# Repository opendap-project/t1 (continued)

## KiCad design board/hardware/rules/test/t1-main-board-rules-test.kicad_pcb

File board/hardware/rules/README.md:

# Main board rules

The T1 main board's own design rules, from the [PCB design constraints](../../docs/specs/pcb-design-constraints.md) (BRD-060). The sources of the manufacturing, assembly and reliability values are keyed at the end of this file.

- `t1-main-board.kicad_dru`: the product rules. Each rule is named after the constraint it enforces and the lowest quality level at which it is mandatory ([RFC 0010](https://github.com/opendap-project/rfcs/blob/main/text/0010-quality-levels.md)): `T1 PCB-H-01 [Q1]: …`.
- `netclasses.toml`: the net classes the rules and the schematic share, with their constraint IDs, design currents and impedance targets.
- `test/`: a test board with one failing and one passing object per rule, built by `make_test_board.py` on libs' `kicad/` test-board tools (submodule `../lib/opendap`).

The KiCad project's rules, [`../t1-main-board/t1-main-board.kicad_dru`](../t1-main-board/), are the composition of the PCBWay HDI fab rules (libs `kicad/` `design-rules/pcbway-hdi`), the OpenDAP craft rules (libs `kicad/` `design-rules/opendap-craft`) and these product rules, in that order, made and checked with `odapkit dru` from `t1-main-board.dru.toml`.

Impedance-controlled net classes are named `<name>_<ohms>D` (differential) or `<name>_<ohms>SE` (single-ended), so the craft rules exempt them from their general width rules (CRAFT-40, CRAFT-43; the composition was checked with every impedance class: no craft or fab report on their tracks). The product rules find the same classes with the same wildcards (PCB-S-14, PCB-W-01). `BAT_SENSE` also matches the `*_???SE` wildcard and is not an impedance class: the product rules leave it out by name.

## Layers

The board is the 6-layer [stackup v3](../../docs/specs/stackup-v3.md), with layer roles by zone (its §3). The rules name KiCad's layers:

| Stackup | L1 | L2 | L3 | L4 | L5 | L6 |
|---|---|---|---|---|---|---|
| KiCad | `F.Cu` | `In1.Cu` | `In2.Cu` | `In3.Cu` | `In4.Cu` | `B.Cu` |
| Role | signal (decoupling and core-rail pours in the core zone) | ground (core and system rails in the core zone) | ground (pours in the power zone) | signal (stripline; pours in the power zone, power or RF ground in the radio zone) | ground, full layer | signal |

Per-class widths are rules on `(layer outer)` (L1, L6) and `(layer inner)` (L4); PCB-S-14 keeps impedance classes off every other inner layer, so "inner" means L4 for them, and its zone rules keep them off L1 in the core zone and off L4 in the power and radio zones. Each width rule is min / opt / max = the stackup width −5 % / exact / +5 %: a 5 % width error moves the impedance by 2–3 %, a third of the fab's ±10 % window, so the rule catches a wrong width while leaving the fab's own corners alone. LPDDR4X keeps 3 × W from every other net on L4 (PCB-S-24). The ground layers of each zone take no other net's tracks or fills (PCB-S-25: L5 everywhere, L2 outside the core zone, L3 outside the power zone), and the I/O zone's `VBUS` nets stay on the outer layers (PCB-P-22).

## Severity

- A rule at Q0 or Q1 whose value has a source is an **error**.
- A rule at Q2 to Q4 is a **warning**, whatever its source (RFC 0010: items above the build's target level are debt, not blockers).
- A rule whose value is still **UNVERIFIED** is a **warning** at any level, and becomes an error when the value is sourced and the level is Q0 or Q1.

Each rule's comment in the `.kicad_dru` names its source; [Sources of the rule values](#sources-of-the-rule-values) lists the keys.

## Conventions the rules rely on

The rules find objects by reference prefix, footprint field, pad fabrication property and rule-area name. The schematic symbols and footprints carry them; a footprint that does not follow them escapes its rules.

| Object | Convention | Rules |
|---|---|---|
| Mounting hole | Footprint reference `H*` (`H1`…`H4`); one pad, NPTH or plated | PCB-H-01 to H-06 |
| Ceramic capacitor (MLCC) | Reference `C*`. A capacitor that is not an MLCC still gets the MLCC rules, which only cost distance | PCB-H-05, PCB-B-03 |
| Edge-mounted part | Reference `J*` (connectors) or `SW*` (side buttons): exempt from the part-to-edge rule, may overhang the edge | PCB-B-01 |
| BGA needing rework access | Footprint field `Rework` = `BGA` (RK3566, LPDDR4X, eMMC) | PCB-D-01 |
| BGA ball pads | Pad fabrication property "BGA pad" (also used by the fab rules) | PCB-H-06 |
| Fiducial | Reference `FID*`; pad fabrication property "Fiducial, global to board" or "Fiducial, local to footprint" | PCB-D-02 to D-04 |
| Test point | Reference `TP*`; pad fabrication property "Test point pad" | PCB-D-06 to D-09 |
| Via in a pad | Via property Filling = Filled and Capping = Capped (IPC-4761 type VII) | PCB-D-10 |
| Heat source | Footprint field `Thermal` = `hot` (converters, eFuses, charger, SoC, PMIC) | PCB-L-01 |
| Battery pocket | Rule area `BATTERY_POCKET`: the pocket's footprint on the board, grown by a 3 mm margin (**UNVERIFIED**) | PCB-L-01 |
| Battery contacts | Rule area `BATTERY_CONNECTOR`: the pocket-floor contact window plus 1 mm, around the six battery contacts and their unfused copper (ADR 0020) | PCB-L-02, L-05 |
| Battery nets | Net classes `PWR_BAT` (P+, P−) and `BAT_SENSE` (mid-cell tap, NTC) in `netclasses.toml` | PCB-L-02, L-05 |
| Empty contact position | Rule area `BATTERY_CONTACT_EMPTY`: the 7.00 × 2.70 mm pad position left empty between P+ and the mid-cell tap | PCB-L-04 |
| Battery contact ESD | Footprint field `ESD` = `battery` on the TPD1E10B06 of the mid-cell tap and NTC; rule area `BATTERY_ESD`: the contact pads grown by 3 mm (**UNVERIFIED**) | PCB-L-08 |
| Panel break tab | Rule area `BREAK_TAB` around each tab or mouse-bite position on the outline, reaching at least 5.08 mm (PCB-B-03) into the board | PCB-B-02, B-03 |
| RK3566 escape | Rule area `BGA_ESCAPE` (existing) | PCB-G-02, W-01, V-01 |
| Analog audio | Rule area `AUDIO_ANALOG` (existing) | PCB-A-07, A-20 |
| Differential pair | Net names ending in `_P` / `_N` (or `+` / `-`), so KiCad couples the pair | PCB-I-01, I-02, I-04, I-05 (pair gap) |
| RF ground cut-out | Rule area `RF_CUTOUT`: the L2 (L5) cut-out under the RF line, 1.6 mm wide and 0.6 mm past each end, on the cut layer and the pour layer of the line's side only (`In1.Cu` + `In2.Cu` for an L1 line, `In4.Cu` + `In3.Cu` for L6), with "keep out copper fills" set so the plane's fill stays out | PCB-R-03 |
| Zones | Rule areas `ZONE_CORE`, `ZONE_AUDIO`, `ZONE_POWER`, `ZONE_IO`, `ZONE_RADIO`, `ZONE_FACEPLATE` (one or more per zone, an area may cover only some layers) and `ZONE_CORRIDOR` ([floorplan v1](../../docs/specs/floorplan-v1.md)) | PCB-S-14 by zone, S-17, S-18, S-25, P-22 |
| Zone of a net | Net class `ZONE_<NAME>` or `ZONE_SHARED` besides the signal class (`netclasses.toml`) | PCB-S-17 |

## Check

```sh
PY=/Applications/KiCad/KiCad.app/Contents/Frameworks/Python.framework/Versions/Current/bin/python3
$PY hardware/rules/test/make_test_board.py
python3 hardware/lib/opendap/kicad/design-rules/tools/check_drc.py hardware/rules/test/t1-main-board-rules-test.kicad_pcb
```

Every rule fires exactly once in the FAIL column and nothing fires in the PASS column.

Rules that overlap the fab and craft rule sets are left to them: silkscreen to pads and vias, silk sizes, 45° routing, acute angles (CRAFT-41, 135° minimum), short segments and the via set live in libs `kicad/` `opendap-craft`. The composition `pcbway-hdi` + `opendap-craft` + these rules compiles under KiCad 10.0.7 with every T1 rule still firing on the test board. The test board has six copper layers (stackup v3); its GND objects are joined by a bus on L5 (`In4.Cu`, the full-layer ground, which takes GND), so the board reports no unconnected items.

## Not checked by DRC

Impedance itself, zone-local ground stitching and zone-boundary fences (PCB-S-19, S-13), the edge margin from a zone-local ground, the maximum pair gap, spacing to other nets (3–5 × W; LPDDR4X on L4 is DRC, PCB-S-24), length matching, skew and delay matching across layers (PCB-I, PCB-S-15), height zones (PCB-Z, including the battery-contact exception of PCB-L-05), copper area per net and via counts for current (PCB-P-01 to PCB-P-03, PCB-P-09), the battery contacts' pad size, pitch and order (PCB-L-04), via count per contact pad and pour symmetry (PCB-L-07), ESD distance (PCB-E-01) and test-pad coverage (PCB-T-02) are layout checks. The contact working height and the liner distance (PCB-L-06) are 3D review and case items. Review items are listed in the specification.

KiCad 10.0.7 can express three more rules, thermal-relief spoke count (`min_resolved_spokes`), differential-pair uncoupled length (`diff_pair_uncoupled`) and differential-pair gap (`diff_pair_gap`, with its maximum and the router's gap), but its report does not name the rule for them ("zone min spoke count", "(<rule> maximum uncoupled length", "(<rule> maximum gap"), so `check_drc.py` cannot attribute them. The pair gap's minimum is checked as a clearance instead (see Layers). They wait for a libs `kicad/` `check_drc.py` that reads those messages; until then they are CHK items below, with the other checks DRC cannot make.

## Review and script items (CHK)

Checklist wording; the level is the lowest at which the item is mandatory.

| ID | Level | Kind | Checklist wording |
|---|---|---|---|
| CHK-H-01 | Q1 | REV | The screw, washer and hole are chosen with the case; the PCB-H rules' 1.4 mm ring is recomputed from them, and H-01, H-02 become errors. |
| CHK-H-02 | Q2 | REV | Plated or non-plated mounting holes decided; if plated, on GND and stitched to the ground planes, and the case boss is insulating or its contact is part of the ESD path. |
| CHK-H-03 | Q1 | REV | No MLCC within the bending zone of a screw is oriented with its length towards the screw; parts near screws are placed with their long axis tangential to the hole. |
| CHK-B-01 | Q1 | REV | Tab and mouse-bite positions agreed with the fab's panel drawing; a `BREAK_TAB` area drawn at each, reaching 5.08 mm into the board. |
| CHK-B-02 | Q1 | REV | MLCCs within 5.08 mm of any broken edge lie parallel to the break line (KYOCERA AVX, Murata guidance; distance in PCB-B-03). |
| CHK-B-03 | Q1 | REV | Every part that overhangs the edge (J*, SW*) matches its case opening in the t1 interface files. |
| CHK-D-01 | Q1 | CHK | Three global fiducials per populated side, not symmetric, and two local fiducials at the RK3566 (PCB-M-09): count pads with the fiducial property per side. |
| CHK-D-02 | Q1 | REV | Polarity and pin-1 marks visible after assembly for every polarised part (diodes, tantalum or polymer capacitors, ICs, connectors). |
| CHK-D-03 | Q1 | REV | Paste on exposed thermal pads in a window pattern per each part's datasheet layout; coverage within the datasheet's range (**UNVERIFIED** generic figure, no IPC-7525 text retrieved). |
| CHK-D-04 | Q1 | CHK | Parts taller than the BGA within the rework clearance of a `Rework` = `BGA` part flagged from the 3D model heights. |
| CHK-D-05 | Q2 | CHK | Test pads 1.0 mm from component bodies (3D model outline), 5 mm from parts over 6.4 mm tall [JD]. |
| CHK-D-06 | Q1 | CHK | One test pad per net where required (PCB-T-02 rails, BRD-040 I2S, BRD-047 UART, BRD-015 SWD). |
| CHK-D-07 | Q1 | CHK | Via tenting set at board level (front and back tented), so only vias the layout opens on purpose are open; the fab order option matches. |
| CHK-D-08 | Q1 | CHK | Naming conventions followed: every mounting hole H*, fiducial pads carry the fiducial property, test pads the test-point property, BGA rework candidates and heat sources their fields. |
| CHK-W-01 | Q1 | CHK | Thermal relief on plane connections of connectors and test pads, at least 2 spokes resolved (PCB-G-07). KiCad `min_resolved_spokes` works but reports "zone min spoke count" without the rule name. |
| CHK-W-02 | Q2 | CHK | Differential-pair uncoupled length within the class limit. KiCad `diff_pair_uncoupled` works but reports "(<rule> maximum uncoupled length" without "rule '…'". The limit itself is **UNVERIFIED** (no source retrieved). |
| CHK-W-03 | Q2 | SIM | Via stubs over 0.30 mm on high-speed pairs simulated (Rockchip HSPCB p. 10 [RK]). |
| CHK-W-04 | Q2 | CHK | No test pad on a high-speed pair (Rockchip HSPCB p. 12 [RK]). Expressible in DRC as a later rule. |
| CHK-L-01 | Q0 | REV | `BATTERY_POCKET` drawn from the case's pocket outline plus the margin; the margin confirmed by the thermal analysis (V4-03). |
| CHK-V-01 | Q3 | REV | Creepage and clearance needs of IEC 62368-1 for the declared markets confirmed for ES1 circuits. |

## KiCad 10.0.7 behaviour found while testing

- **Angles are bare numbers.** `track_angle (min 90deg)` makes KiCad drop the whole file silently; `(min 90)` works. Each acute corner is reported twice, once per segment order.
- **A rule with `min 0` loses its name.** A `courtyard_clearance (min 0mm)` overlap is reported as the built-in "Courtyards overlap" without "(rule …)", so it cannot be tested; any value above zero is named.
- **Courtyards are measured from the line's centre; Edge.Cuts lines from their outer edge** in physical rules, and from their centre in `edge_clearance`.
- **Courtyard distance is per side.** A front part and a back footprint are not compared; hence the area-based PCB-L-01.
- **`physical_clearance` against a courtyard needs `A.Type == 'Footprint'`.** Without it the courtyard graphic and the footprint are both reported (two violations for one fault). A pad and a courtyard are on different layers and are never compared.
- **Silk to edge:** a silk line within the distance is reported only when the edge clips it; text is reported, but its distance to an internal cutout does not follow the text's position, so the test uses a clipped line.
- **`connection_width` fires** (tested with zone necks), but only about 0.01 mm or more below the limit; the test board uses 0.02 mm.
- **`min_resolved_spokes` and `diff_pair_uncoupled` work but are not named** in the report (CHK-W-01, CHK-W-02).
- **Unknown properties fail silently**: an assertion on a misspelt property fails on every object, which the PASS column catches. Via properties `Filling`, `Capping`, `Front_tenting`, `Back_tenting` and `Enable_Teardrops` exist with values `Filled`, `Capped`, `Tented`, `Not tented`.
- **`memberOfFootprint('H*')` is false for the footprint itself**; conditions on footprints use `Reference == 'H*'`.

## Sources of the rule values

Fetched 2026-10-24 unless stated.

| Key | Source | Kind |
|---|---|---|
| IPC | IPC-2221B Table 6-1 as reproduced in Altair Pollex documentation, "IPC Material": <https://help.altair.com/pollex/topics/pollex/verification/dfe_ipc_material_r.htm> | Secondary |
| F1 | ISO 7089 flat washer dimensions, fasten.it norm table: <https://www.fasten.it/en/norms/norm/iso_7089> (M2: d1 2.2, d2 5, h 0.3; M1.6: 1.7, 4, 0.3) | Secondary (vendor copy of the standard) |
| MU | Murata FAQ on chip capacitor mounting near screw holes: <https://www.murata.com/en-global/support/faqs/capacitor/ceramiccapacitor/mnt/0030> and the GRM data-sheet caution ("as far away from the screw holes as possible") | Primary |
| DK | DigiKey TechForum, "Ceramic Capacitor Failure: Design Solutions & Mitigating Board Flex Cracking", quoting KYOCERA AVX: <https://forum.digikey.com/t/ceramic-capacitor-failure-design-solutions-mitigating-board-flex-cracking/26195> | Secondary |
| JL | JLCPCB PCB capabilities (Legend, Outline, panelisation): <https://jlcpcb.com/capabilities/pcb-capabilities> | Primary (another fab) |
| JD | JLCPCB blog, "PCB Test Points and Smart DFT": <https://jlcpcb.com/blog/pcb-test-points-and-smart-dft> | Secondary |
| LC | LCSC blog, "How to Properly Place Fiducial Marks on PCBs": <https://www.lcsc.com/blog/how-to-properly-place-fiducial-marks-on-pcbs-a-step-by-step-guide/> | Secondary |
| AP | ALLPCB, "Non-Plated Through Holes: Design Rules": <https://www.allpcb.com/allelectrohub/non-plated-through-holes-design-rules-for-optimal-performance-and-reliability> | Secondary |
| RK | Rockchip RK3568 High Speed PCB Design Guide V1.0.0, cited by page | Primary |
| P1–P20 | The prototype fab's published pages, as keyed in libs' `kicad/` `pcbway-*` rule sets (fetched 2026-10-22): P1 capabilities, P2 advanced, P3 HDI, P11 via-in-pad, P16 order options, P20 assembly reminders | Primary |
| KiCad | KiCad 10.0.7 PCB Editor manual, custom rules (bundled `pcbnew.html`), and the behaviour listed above | Primary |

Not retrieved, so not used for any value: IPC-7351B courtyard excess table, IPC-7095 rework clearances, IPC-A-610, IPC-2152, IPC-7525 paste, SMEMA 3.1 text, TI and Intel high-speed layout guides for uncoupled length, the fab's pages on fiducials, test points and tab clearance, and any Li-ion cell maker's heat-source distance.

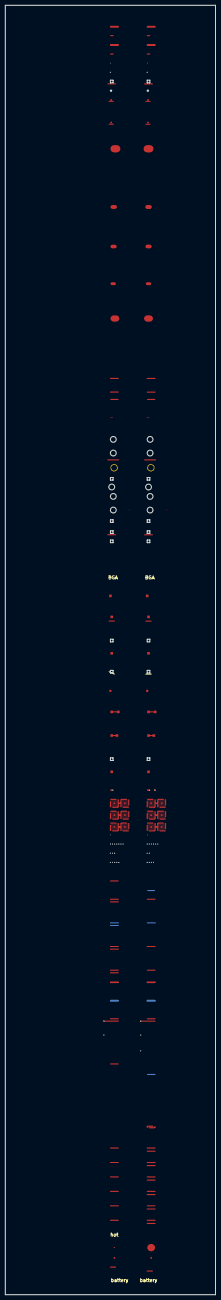
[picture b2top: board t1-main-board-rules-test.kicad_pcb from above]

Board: 6 copper layers, 80.0 x 490.7 mm, 74 parts (0 on the bottom side), 10 nets.

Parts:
C1, C2, C3, C4, C5, C6: test
D1, D2: test
FID1, FID2: test
H1, H2, H3, H4, H5, H6, H7, H8, H9, H10, H11, H12, H13, H14: test
R1, R2, R3, R4, R5, R6, R7, R8, R9, R10, R11, R12, R13, R14, R15, R16, R17, R18, R19, R20, R21, R22, R23, R24, R25, R26, R27: test
TP1, TP2, TP3, TP4, TP5, TP6, TP7, TP8, TP9, TP10, TP11, TP12, TP13, TP14: test
U1, U2, U3, U4, U5, U6, U7, U8, U9: test

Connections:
DDR_50SE_1: R18.1, R19.1
DDR_50SE_2: R20.1, R21.1
N49: TP7.1, TP8.1
N50: TP9.1, TP10.1
N51: R9.1, TP11.1
N52: R10.1, TP12.1
N58: R14.1, R15.1
N59: R16.1, R17.1
N60: R22.1, R23.1
N61: R24.1, R25.1

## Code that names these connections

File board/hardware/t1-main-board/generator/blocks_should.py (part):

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    grp(col, lambda: link_group(s, "LINK_M", "vcc3v3_sys", "HAPTIC_VDD", variants, "Link #19"))
    grp(col, pads(s, "LRA contacts (BOM v1 line 124)", ("LRA_P", "LRA_N")))
    s.iface_rows = [["I2C2_SCL, I2C2_SDA", "Bidirectional", "0x5A; pull-ups on blk.soc-pmuio"],
                    ["HAPTIC_EN", "Input", "Expander P04, pulled down on blk.gpio-expander: standby"]]
    s.rail_rows = [["HAPTIC_VDD", "1 µF", "SLOS854D Table 32"], ["HAPTIC_REG", "1 µF", "SLOS854D Table 32"]]
    corner_notes(s, [
        "1. Function: DRV2605L closed-loop LRA driver with auto-resonance (BRD-058, should) for the",
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
def draw_tpm(s, variants):
    f = Flow(s)
    pins = {"SCL": "I2C2_SCL", "SDA": "I2C2_SDA", "RST#": "TPM_RST_N", "TEST#": "TPM_VDD",
            "GPIO_00": None, "GPIO_01": None, "GPIO_02": None, "NCI": None, "NC": None, "I2C_PIRQ#": "TPM_PIRQ_N",
            "VDD": "TPM_VDD", "NCI/VDD": "TPM_VDD", "GND": "GND", "NCI/GND": "GND", "EP": "GND"}
    grp(f, lambda: ic_group(
        s, "SLB9673 TPM 2.0 at I2C2 0x2E (BOM v1 line 122)", "infineon", "SLB9673XU20FW2613XTMA1", pins,
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              [("R_2k2", "TPM_VDD", "TPM_RST_N")]], pad_left=15.24, rows_dx=5.08))
    grp(f, lambda: link_group(s, "LINK_M", "vcca1v8_pmu", "TPM_VDD", variants, "Link #20"))
    s.iface_rows = [["I2C2_SCL, I2C2_SDA", "Bidirectional", "0x2E; pull-ups on blk.soc-pmuio"],
                    ["TPM_RST_N", "Input", "GPIO0_D3; 2.2 kΩ pull-up here wins over the SoC pull-down"],
                    ["TPM_PIRQ_N", "Output", "Open drain; pull-up on vcc_1v8 on blk.soc-vccio-a"]]
    s.rail_rows = [["TPM_VDD", "1 µF + 3 x 100 nF", "SLB9673 DS Figure 2"]]
    corner_notes(s, [
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
# ---------------------------------------------------------------------- blk.rp2354

RP_GPIO = {"GPIO0": "RP_UART_TX", "GPIO1": "RP_UART_RX", "GPIO2": "RP_IRQ", "GPIO3": "RP_SPARE",
           "GPIO4": "RP_TAP_BCLK", "GPIO5": "RP_TAP_LRCK", "GPIO6": "RP_TAP_SDO0", "GPIO7": "RP_TAP_DSD_L",
           "GPIO8": "RP_TAP_DSD_R"}        # pinout v1 §3, Coprocessor: RP2354A GPIO allocation (2026-10-26)
TAPS = [("I2S_BCLK", "RP_TAP_BCLK"), ("I2S_LRCK", "RP_TAP_LRCK"), ("I2S_SDO0", "RP_TAP_SDO0"),
        ("DSD_L", "RP_TAP_DSD_L"), ("DSD_R", "RP_TAP_DSD_R")]

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def core_tables(s):
    s.iface_rows = [
        ["RP_UART_TX, RP_UART_RX", "Bidirectional", "UART0 to the SoC's UART0 (PMUIO2); SoC pull-downs park both"],
        ["RP_IRQ", "Output", "GPIO2 to 1V20 (wake): 100 kΩ pull-down on the host side (blk.soc-vccio-b), no wake when off or unfitted"],
        ["RP_RUN, RP_SWCLK, RP_SWDIO", "Input", "SoC open drain / SWD (VCCIO6); parked low while the rails are off (G4)"],
        ["RP_BOOTSEL_DRV", "Input", "N-FET gate, 100 kΩ pull-down on the host side (blk.soc-vccio-b): normal boot"],
        ["RP_USB_DP, RP_USB_DM", "Bidirectional", "USB_HOST2 (EHCI/OHCI) of the SoC"],
        ["I2S_BCLK, I2S_LRCK, I2S_SDO0, DSD_L, DSD_R", "Input", "Taps on FT GPIO4-8 through 0 Ω (G4); no load on the DAC path"],
    ]
    s.rail_rows = [["RP_IOVDD_1V8", "100 nF at the oscillator", "ECS-2016MV (value: capture choice)"]]
    corner_notes(s, [
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        "3. IOVDD at 1.8 V: firmware sets VOLTAGE_SELECT = 1 for bank 0 at boot (DS §6.1.1).",
        "4. QSPI pads go to the in-package flash only: open here (HDG §3.1); BOOTSEL pulls QSPI_SS low",
        "   through 1 kΩ and the N-FET. USB (full speed): 27 Ω at the RP2354A (DS Table 1678), 2.2 Ω at the SoC.",
        "5. GPIO allocation (pinout v1 §3, 2026-10-26): UART0 GPIO0/1, RP_IRQ GPIO2, spare GPIO3 (pad),",
        "   taps GPIO4-8 for one PIO IN (DS §11.5.6); GPIO9-29 open. The I2C2 option is not wired (G16).",
    ])


RP_RAILS = [
        ["RP_IOVDD_1V8", "6 x 100 nF", "DS §6.1: 100 nF per power pin"],
        ["RP_3V3", "4.7 µF (VREG_VIN) + 3 x 100 nF", "DS §6.1, §6.3.8 (CIN 4.7 µF); QSPI_IOVDD, USB_OTP_VDD, ADC_AVDD"],
        ["RP_DVDD", "4.7 µF at pin 23 + 2 x 100 nF", "HDG §2.2.1: 4.7 µF on the furthest DVDD pin"],
        ["RP_VREG_AVDD", "33 Ω + 4.7 µF", "HDG p. 7 (RC filter)"],
        ["vcc3v3_sys, vcc_1v8", "1 µF at each switch input", "Capture choice (SLVSEN5B)"],
]
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
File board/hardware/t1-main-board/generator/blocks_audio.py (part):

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               {"VIN": "VSYS_LV_AUDIO", "EN": "AUDIO_LN_EN", "MODE": "GND", "STOP": "GND", "VSET": "AUDIO_VSET",
                "SW": "AUDIO_SW", "VOS": "AUDIO_2V2_SRC", "GND": "GND"})
        g.add(u.bbox)
        g.add(two_pin_box(s, "L_DFE201610E_2R2", u.bbox[2] + 22.86, 93.98, "AUDIO_SW", "AUDIO_2V2_SRC", prefix="L"))
        g.add(under(s, u.bbox, [("C_4u7_0402_10V", "VSYS_LV_AUDIO", "GND"), ("R_4k32", "AUDIO_VSET", "GND"),
                                ("C_10u_0402_4V", "AUDIO_2V2_SRC", "GND")], x=u.bbox[0] + 2.54))
        return g.close()
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            g.add(prow(s, 101.6 - 3.81, 101.6 + 5 * 15.24 + 5.08, [("R_4k99", f"{n}_ADR", "GND")]))
        return g.close()
    grp(f, serial)
    pins = {"SCL": "DAC_I2C_SCL", "SDA": "DAC_I2C_SDA", "ADR": "GND" if master else f"{n}_ADR",
            "RESET": "DAC_RST_N", "SDIN1": f"{n}_SDIN", "SCLK1": f"{n}_SCLK", "LRCK1": f"{n}_LRCK",
            "DSDA/SDIN2": f"{n}_DSDA", "DSDB/LRCK2": None, "DSDCLK/SCLK2": f"{n}_DSDCLK",
            "XTI/MCLK": f"MCLK_{side}", "XTO": None, "HP_DETECT": "GND",
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        g.add(u.bbox)
        x0 = u.bbox[2] + 5.08
        s.flag_net("HPA_BOOST_VIN", since=s.mark()[1], side="right")   # fed through the 100 Ω filter
        g.add(two_pin_box(s, "R_100", x0 + 17.78, u.bbox[1] + 7.62, "VSYS_LV_AUDIO", "HPA_BOOST_VIN"))
        g.add(two_pin_box(s, "L_DFE252012F_4R7", x0 + 17.78, u.bbox[1] + 22.86, "VSYS_LV_AUDIO", "HPA_BOOST_SW", prefix="L"))
        yd = u.bbox[1] + 38.1
        d = part(s, "Diode", "PMEG2010AEH", x0 + 22.86, yd, {"2": "", "1": ""}, key="D_PMEG2010AEH", angle=180,
                 prefix="D")
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                "VCC": "HPA_N7_VCC", "FB": "HPA_N7_FB", "PG": None, "PGND": "AUDIO_N7V0", "AGND": "AUDIO_N7V0"})
        g.add(u.bbox)
        x0 = u.bbox[2] + 5.08
        g.add(two_pin_box(s, "L_XGL4020_222", x0 + 17.78, u.bbox[1] + 7.62, "HPA_N7_SW", "GND", prefix="L"))
        g.add(divider(s, x0 + 15.24, u.bbox[1] + 33.02, "AUDIO_N7V0", "HPA_N7_FB", "GND", "R_16k5", "R_100k_0603",
                      cff="C_22p_0402", cff_on="bottom", flag_top=True))
        g.add(prow(s, x0 + 50.8, u.bbox[1] + 33.02, [("C_100n_0402", "HPA_N7_BOOT", "HPA_N7_SW"),
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        g = Group(s, "-7 V enable level shifter (SNVA856B Fig. 7-1)")
        q1 = part(s, "Transistor_FET", "DMG1012T", 127.0, 116.84, {"1": "HPA_RAIL_EN", "3": "HPA_N7_LS_G", "2": "GND"},
                  key="Q_DMG1012T", prefix="Q")
        g.add((101.6, 101.6, 139.7, 129.54))     # the gate's HPA_RAIL_EN label inside the group
        g.add(prow(s, 147.32, 109.22, [("R_100k", "VSYS_AUDIO", "HPA_N7_LS_G")]))
        part(s, "Transistor_FET", "DMP3099L", 175.26, 116.84, {"1": "HPA_N7_LS_G", "3": "VSYS_AUDIO", "2": "HPA_N7_LS_D"},
             key="Q_DMP3099L", prefix="Q")
        g.add((160.02, 101.6, 190.5, snap_up(124.46 + len("HPA_N7_LS_D") * 1.16 + 2.54)))   # the drain label below
        g.add(prow(s, 200.66, 109.22, [("R_100k", "HPA_N7_LS_D", "HPA_N7_EN"), ("R_100k", "HPA_N7_EN", "AUDIO_N7V0")]))
        return g.close()
    grp(f, shifter)
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        x = 101.6
        for i in range(2):
            tag = f"HPA_{sign}6_{'AB'[i]}"
            pins = {"IN": vin, "EN/UV": "HPA_LDO_EN", "PGFB": vin, "ILIM": f"{tag}_ILIM", "SET": setn,
                    "OUT": tag, "OUTS": tag, "PG": None, "GND": "GND"}
            if name == "LT3094EDD":
                pins["VIOC"] = None
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
    def ties():
        g = Group(s, "Reference net ties at the sleeve (PCB-A-03, -16)")
        g.add(two_pin_box(s, "NT_SENSE", 101.6, 101.6, "HPSE_REF_L", "GND"))
        g.add(two_pin_box(s, "NT_SENSE", 101.6, 114.3, "HPSE_REF_R", "GND"))
        return g.close()
    grp(f, ties)
    grp(f, lambda: tvs_group(s, "ESD and detect (BOM v1 line 36)", ("HPSE_L", "HPSE_R", "HP_DET_SE")))
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    corner_notes(s, [
        "1. Function: 4.4 mm 5-pole jack (L+, L-, R+, R-, GND; JEITA RC-8141C, BOM v1 line 31);",
        "   TPD1E10B06 on each leg and the detect line (line 36).",
        "2. Absent state: passive; left off only with blk.hpa-bal (blk.hp-out-bal). Detect: pin 10 to HP_DET_BAL,",
        "   pin 9 to ground (switch state UNVERIFIED on the drawing), read by expander P11 with its pull-up on the",
        "   host side, so the line reads \"absent\" with the jack left off.",
        "3. Pin-to-pad assignment UNVERIFIED (libs kicad/ note): check against a sample before boards.",
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       {"1A": "I2C2_SCL", "1B": "DAC_I2C_SCL", "1C": "DAC_DIG_1V8", "2A": "I2C2_SDA", "2B": "DAC_I2C_SDA",
        "2C": "DAC_DIG_1V8", "VCC": "vcca1v8_pmu", "GND": "GND"})
    for i, (net, alt) in enumerate((("SCL", "I2C2_SCL"), ("SDA", "I2C2_SDA"))):
        two_pin_v(s, "R_4k7", 116.84 + i * 15.24, y0 + 20.32, "DAC_DIG_1V8", f"DAC_I2C_{net}", blk)   # rail values apart
        two_pin_h(s, "R_0_0402", 129.54, y0 + 45.72 + i * 10.16, alt, f"DAC_I2C_{net}", blk,
                  extra={"Alternate": "dac-i2c-bypass"}, dnp=True)
    y0 = y0 if y_right is None else y_right
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        ("R_100k", net, "GND") for net in ("DAC_RST_N", "DAC_VP_EN", "DAC_DIG_EN", "AUDIO_LN_EN", "HPA_SE_EN",
                                           "HPA_BAL_EN", "HPA_LDO_EN", "HPA_RAIL_EN", "RP_IRQ", "RP_BOOTSEL_DRV")]
    for i, (key, a, b) in enumerate(pulls):
        two_pin_v(s, key, 180.34 + i * 19.05, y0 + 25.4, a, b, blk)     # room above for RP_BOOTSEL_DRV
    for i, (a, b) in enumerate((("I2S_BCLK_RX", "I2S_BCLK"), ("I2S_LRCK_RX", "I2S_LRCK"))):
        two_pin_h(s, "R_0_0402", 205.74 + i * 66.04, y0 + 48.26, a, b, blk,
                  extra={"Alternate": "i2s-rx-clocks"}, dnp=True)
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
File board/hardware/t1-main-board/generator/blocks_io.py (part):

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
PORTS = {"P00": "FP_IO_EN", "P01": "HAT_VBUS_DISCH", "P02": "HAT5V_EN", "P03": "USB_SRC_ON", "P04": "HAPTIC_EN",
         "P05": None, "P06": "WL_PWR_EN", "P07": "WL_PD_HOLD_N", "P10": "HP_DET_SE", "P11": "HP_DET_BAL",
         "P12": "FP_DET_N", "P13": "FP_GPIO0", "P14": "FP_GPIO1", "P15": "EFUSE_HAT5V_FLT_N",
         "P16": "EFUSE_5V_FLT_N", "P17": "EFUSE_VBUS_FLT_N"}


def draw_expander(s, variants):
    f = Flow(s)
    pins = dict(PORTS)
    pins.update({"SCL": "I2C2_SCL", "SDA": "I2C2_SDA", "INT": "EXP_INT_N", "RESET": "EXP_RESET_N",
                 "ADDR": "vcc3v3_sys", "VCCI": "vcca1v8_pmu", "VCCP": "vcc3v3_sys", "GND": "GND", "EP": "GND"})
    grp(f, lambda: ic_group(
        s, "TCA6416A at I2C2 0x21 (BOM v1 line 93)", "texas-instruments", "TCA6416ARTWR", pins,
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        rows=[[("C_100n_0402", "IMU_VDD", "GND"), ("C_100n_0402", "IMU_VDD", "GND")]]))
    grp(f, lambda: link_group(s, "LINK_L10", "vcca1v8_pmu", "IMU_VDD", variants, "Link #32"))
    s.iface_rows = [["I2C2_SCL, I2C2_SDA", "Bidirectional", "0x6A (SA0 low); pull-ups on blk.soc-pmuio"],
                    ["IMU_INT1", "Output", "GPIO0_C5 (PMUIO2), wake on motion; SoC pull-down: no wake unfitted"]]
    s.rail_rows = [["IMU_VDD", "100 nF at Vdd, 100 nF at Vdd_IO", "DS13510 §6 (C1, C2)"]]
    corner_notes(s, [
        "1. Function: LSM6DSV16X 6-axis IMU, wake on motion through INT1 (BRD-032, should).",
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
    def mode():
        g = Group(s, "SD_MODE select position (DS Figure 5)")
        g.add(two_pin_box(s, "R_0_0402", 101.6, 101.6, "SPK_SD_MODE", "SPK_SD"))
        return g.close()
    grp(f, mode)

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        return g.close()
    grp(f, pads)
    s.iface_rows = [["SPK_BCLK, SPK_LRCK, SPK_SDIN", "Input", "I2S3_M0 at 3.3 V; 22 Ω at the SoC for the clocks"],
                    ["SPK_SD_MODE", "Input", "GPIO3_A6, SoC pull-down and the 100 kΩ internal pull-down: shutdown"]]
    s.rail_rows = [["SPK_VDD", "10 µF + 100 nF", "MAX98357A Rev 11 p. 33"]]
    corner_notes(s, [
        "1. Function: MAX98357A mono class-D amplifier for the internal speaker (0.7 W, BOM line 33).",
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        g = Group(s, "Series resistors (HDG p. 52)")
        for i, n in enumerate(("CLK", "CMD", "D0", "D1", "D2", "D3")):
            g.add(two_pin_box(s, "R_22", 101.6, 101.6 + i * 10.16, f"SD_{n}", f"SD_{n}_C"))
        g.add(two_pin_box(s, "R_100", 101.6, 101.6 + 6 * 10.16, "SD_DET_N", "SD_DET_C"))
        return g.close()
    grp(f, series)

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        ["PWRON_N", "Output", "RK809 PWRON (blk.pmic, 100 nF there); also blk.maskrom through the BAT54"],
        ["SARADC_VOLUP", "Output", "SARADC_VIN0: 10 kΩ to vcca_1v8 and 1 nF on blk.soc-pmuio; reads released"],
        ["VOLDN_N", "Output", "SARADC_VIN1 and the MaskROM gate: 100 kΩ to vcca1v8_pmu here, 1 nF at the SoC"],
        ["ACTION_BTN_N", "Output", "GPIO0_C2 wake: 4.7 kΩ to vcca1v8_pmu on blk.soc-pmuio; reads released"],
    ]
    corner_notes(s, [
        "1. Function: the four body buttons (T1-014, T1-015; BRD-016, -017, -035, -036): Power to the",
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
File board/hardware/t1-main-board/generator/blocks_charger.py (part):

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path from the BQ25798 BAT node to the six battery contacts, and the fuel gauge.

Sources: board ADRs 0014, 0017, 0020; BOM v1 lines 39-48, 104, 115, 120, 142; power tree v0 §2,
§4.7, §4.7.1; pinout v1 (I2C1, CHG_INT_N, expander P02 and P03); feature blocks §3 records 7 and 8;
TI SLUSDV2C (BQ25798), SLVSEA3F (TPS2121), SLUSE07B Figure 9-1 (BQ28Z610-R1); the parts'
datasheets, as cited in the libs generator data."""

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
def draw_core(s, variants):
    f = Flow(s)
    pins = {"VBUS": "VBUS_CHG", "VAC1": "VBUS_CHG", "VAC2": "VBUS_CHG", "ACDRV1": "GND", "ACDRV2": "GND",
            "D+": None, "D-": None, "SCL": "I2C1_SCL", "SDA": "I2C1_SDA", "CE": "CHG_CE", "QON": "CHG_QON",
            "TS": "BAT_NTC", "ILIM_HIZ": "CHG_REGN", "PROG": "CHG_PROG",
            "PMID": "CHG_PMID", "BTST1": "CHG_BTST1", "SW1": "CHG1_SW", "SW2": "CHG2_SW", "BTST2": "CHG_BTST2",
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
    def power_stage():
        g = Group(s, "Inductor, input and output capacitors (SLUSDV2C §8.2.2)")
        g.add(two_pin_box(s, "L_XGL4015_102", 109.22, 101.6, "CHG1_SW", "CHG2_SW", prefix="L"))
        y = 127.0
        for row in ([("C_10u_0805_25V", "VBUS_CHG", "GND")] * 2 + [("C_100n_0402_50V", "VBUS_CHG", "GND")],
                    [("C_10u_0805_25V", "CHG_PMID", "GND")] * 3 + [("C_100n_0402_50V", "CHG_PMID", "GND")]):
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               prefix="Q", extra={"Constraints": "PCB-L-09"})
        g.add(q.bbox)
        x = q.bbox[2] + 22.86
        g.add(two_pin_box(s, "F_5A", x, 101.6, "BAT_F", "BAT_P", prefix="F"))
        g.add(two_pin_box(s, "R_100", x, 116.84, "BAT_F", "CHG_BATP"))
        part(s, "Device", "D_TVS", x + 25.4, 101.6 + 10.16, {"2": "BAT_P", "1": "GND"}, key="D_TVS_DNP", angle=90,
             prefix="D", dnp=True, extra={"Alternate": "p-plus-tvs"}, in_bom=False, ref_at=(x + 25.4 + 5.4, 110.49), val_at=(x + 25.4 + 4.9, 113.03))
        g.add((x + 25.4 - 5.08, 101.6 + 10.16 - 10.16, x + 25.4 + 12.7, 101.6 + 10.16 + 10.16))
        return g.close()
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
def draw_gauge(s, variants):
    f = Flow(s)
    pins = {"VC1": "GAUGE_VC1", "SRP": "GAUGE_SRP", "SRN": "GAUGE_SRN", "TS1": "GAUGE_TS1", "SCL": "GAUGE_SCL",
            "SDA": "GAUGE_SDA", "VC2": "GAUGE_VC2", "PBI": "GAUGE_PBI", "PACK": "GAUGE_PACK", "CHG": None,
            "DSG": None, "VSS": "BAT_N", "PWPD": "BAT_N"}
    grp(f, lambda: ic_group(
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
    def sense():
        g = Group(s, "Sense resistor, low side, Kelvin (ADR 0017 item 4)")
        g.add(two_pin_box(s, "R_SENSE_3m", 116.84, 101.6, "BAT_N", "GND", stub=7.62,
                          extra={"Constraints": "PCB-P-01"}))
        s.flag_at(116.84 - 3.81 - 5.08, 101.6, "down", 2.54)       # BAT_N: no output pin drives it
        g.add((101.6, 96.52, 132.08, 114.3))
        return g.close()
    grp(f, sense)
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
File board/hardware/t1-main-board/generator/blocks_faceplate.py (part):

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    14: "FP_DSI_CLK_P", 15: "FP_DSI_CLK_N", 16: "GND", 17: "FP_I2C_SCL", 18: "FP_I2C_SDA", 19: "FP_SPI_SCLK",
    20: "FP_SPI_MOSI", 21: "FP_SPI_MISO", 22: "FP_SPI_CS_N", 23: "FP_DBI_DC", 24: "FP_TP_INT", 25: "FP_TP_RST_N",
    26: "FP_LCD_RST_N", 27: "FP_LCD_TE", 28: "FP_HID_INT_N", 29: "FP_ALS_INT_N", 30: "LED_R", 31: "LED_G",
    32: "LED_B", 33: "GND", 34: "PDM_CLK0_FP", 35: "PDM_DATA0", 36: "FP_DET_N", 37: "FP_GPIO0", 38: "FP_GPIO1",
    39: "GND", 40: "MIC_1V8_FP", 41: "FP_1V8", 42: "FP_3V3", 43: "FP_3V3", 44: "FP_VCI", 45: "BL_LEDK",
    46: "BL_LEDA", 47: None, 48: None, 49: None, 50: None, 51: None,
}
LOW_SPEED = [CONTACTS[c] for c in range(17, 39) if CONTACTS[c] not in ("GND",)]   # 21 lines (BOM v1 line 75)
LOW_SPEED_ARRAY = [n for n in LOW_SPEED if n != "FP_GPIO1"]                       # 20 lines on 5 arrays


def switch_group(s, title, part_name, pins, rows, extra=None):
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    def esd():
        # one group for every array at the connector, four per row: the low-speed lines four per
        # array, then the DSI pairs, one pair per two channels, flow-through as the TPD4E05U06 pins
        # run (CLK alone on the third array, its other two channels open). FP_GPIO1, the
        # 21st low-speed line, takes a single TPD1E10B06 in the detect group (BOM v1 line 75).
        g = Group(s, "ESD: 5 x TPD4E05U06 low-speed, 20 lines (BOM v1 line 75); 3 x TPD4E05U06 DSI, "
                     "10 lines (line 72)")
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               ("R_100k", "FP_IO_EN", "GND")]]), newline=True)

    def detect():
        # the spare FP_GPIO1 takes its ESD here: one TPD1E10B06 (BOM v1 line 75)
        g = Group(s, "Detect, spares, FP_GPIO1 ESD")
        b = g.add(prow(s, 101.6, 109.22, [("R_10k", "vcc3v3_sys", "FP_DET_N"), ("R_100k", "FP_GPIO0", "GND"),
                                          ("R_100k", "FP_GPIO1", "GND")]))
        x = snap(b[2] + 7.62)
        part(s, "Device", "D_TVS", x, 101.6, {"2": "FP_GPIO1", "1": "GND"}, key="D_TPD1E10B06", angle=90,
             prefix="D", ref_at=(x + 2.54 + 2.9, 100.33), val_at=(x + 2.54 + 5.8, 102.87))
        g.add((x - 5.08, 101.6 - 7.62 - len("FP_GPIO1") * 1.16, x + 15.24, 101.6 + 12.7))
        return g.close()
    # the links in a column between the switches; their Kelvin pads are the rail test pads (PCB-T-02)
    col = Flow(s, x0=snap(f.x + 0.0), y0=f.y)
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        ["LED_R, LED_G, LED_B", "Output", "From blk.status-led (LP5521 current sources): open with the LP5521 unfitted"],
        ["PDM_CLK0_FP, PDM_DATA0", "Bidirectional", "blk.mic-main: clock through 22 Ω; data to the SoC"],
        ["FP_IO_EN", "Input", "Expander P00, 100 kΩ pull-down here: both switches off"],
        ["FP_DET_N, FP_GPIO0, FP_GPIO1", "Bidirectional", "Expander P12-P14; detect pulled up: absent"],
        ["FP_VCI, MIC_1V8_FP, BL_LEDA, BL_LEDK", "Supply", "From blk.fp-display, blk.mic-main, blk.fp-backlight"],
    ]
    s.rail_rows = [["vcc3v3_sys, FP_3V3_SRC", "1 µF at VIN and VOUT", "SLVSFJ2B (value: capture choice)"],
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        "   against the Hirose drawing: pinout v1 §8.1.",
        "6. Links (power tree §4.12): #23 FP_3V3, 0.1 Ω (80 mA, 8 mV); #31 FP_1V8, 1 Ω (5 mA, 5 mV).",
        "7. ESD at the connector: DSI CLK and D0-D3 on 3 x TPD4E05U06 (line 72, 0.42-0.5 pF, one pair per",
        "   two channels); 20 low-speed lines on 5 x TPD4E05U06 and FP_GPIO1 on a TPD1E10B06 (line 75).",
    ])


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
    def stage():
        g = Group(s, "Inductor, rectifier, output capacitor (lines 52, 53)")
        g.add(two_pin_box(s, "L_XFL3012_223", 109.22, 101.6, "BL_SW", "VSYS_LV_BL", prefix="L"))   # pad 1, the start lead, on SW
        part(s, "Diode", "PMEG6010CEH", 116.84, 116.84, {"1": "BL_LEDA", "2": "BL_SW"}, key="D_PMEG6010CEH", angle=180,
             prefix="D", ref_at=(116.84, 116.84 - 6.35), val_at=(116.84, 116.84 - 3.81), stub=5.08)
        g.add((96.52, 106.68, 137.16, 119.38))
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    s.iface_rows = [
        ["FP_I2C_SCL, FP_I2C_SDA", "Bidirectional", "I2C3_M1 at 3.3 V; pulled to FP_3V3, so nothing back-powers"],
        ["FP_HID_INT_N, FP_ALS_INT_N", "Output", "Open drain on the faceplate; read low while FP_3V3 is off"],
        ["FP_SPI_*, FP_DBI_DC, FP_TP_*, FP_LCD_*", "Bidirectional", "SPI1_M1 and GPIO on VCCIO5; SoC pulls"],
    ]
    corner_notes(s, [
        "1. Function: the faceplate control bus and its interrupts (record 24): I2C3 at 400 kHz with",
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
    def series():
        g = Group(s, "PDM clock series (HDG p. 72)")
        g.add(two_pin_box(s, "R_22", 101.6, 101.6, "PDM_CLK0", "PDM_CLK0_FP"))
        return g.close()
    grp(f, series)
    grp(f, lambda: link_group(s, "LINK_L10", "MIC_1V8", "MIC_1V8_FP", variants, "Link #34"))
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        return g.close()
    grp(f, probes)
    s.iface_rows = [
        ["MIC_EN", "Input", "GPIO4_C0, SoC pull-down: off"],
        ["MIC_1V8, MIC_1V8_FP", "Supply out", "Off with MIC_EN low; MIC_1V8_FP to contact 40, MIC_1V8 also to blk.mic-ambient"],
        ["PDM_CLK0, PDM_CLK0_FP", "Output", "PDM_CLK0_M1, parked low while MIC_1V8 is off (G10)"],
    ]
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        "3. Link #34 (L10, 10 Ω) on the faceplate branch, MIC_1V8_FP; the ambient branch takes link #35",
        "   on blk.mic-ambient (power tree §4.12, G10).",
        "4. Open: the privacy-LED gate (BOM v1 line 35: DMG1012T, gate = MIC_1V8, LED anode from",
        "   FP_3V3) has no faceplate contact in pinout v1 §8.2; it is drawn when the LED's place is set.",
    ])

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
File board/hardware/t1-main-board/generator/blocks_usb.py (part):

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
    def series():
        g = Group(s, "D± series 2.2 Ω (HDG p. 56); VBUSDET divider (HDG Figure 2-43)")
        g.add(two_pin_box(s, "R_2R2", 101.6, 101.6, "USBC_DP_C", "USBC_DP"))
        g.add(two_pin_box(s, "R_2R2", 101.6, 111.76, "USBC_DM_C", "USBC_DM"))
        g.add(prow(s, 134.62, 109.22, [("R_10k", "USBC_VBUS", "USBC_VBUSDET"), ("R_15k", "USBC_VBUSDET", "GND")]))
        return g.close()
    grp(f, series)
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
    def stage():
        g = Group(s, "Inductor and enable OR (BOM v1 line 91)")
        g.add(two_pin_box(s, "L_XGL4015_102", 109.22, 101.6, "P5V1_SW", "P5V1_SRC", prefix="L"))
        for i, src in enumerate(("HAT5V_EN", "USB_SRC_ON")):
            y = 121.92 + i * 15.24
            from blocks_charger import or_diode      # text above the body, labels on stubs clear of it
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        g = Group(s, "VBUS discharge (BOM v1.13 changes item 3)")
        q = part(s, "Transistor_FET", "DMG1012T", 121.92, 109.22, {"1": "HAT_VBUS_DISCH", "3": "HAT_DISCH_D", "2": "GND"},
                 key="Q_DMG1012T", prefix="Q")
        g.add((snap(116.84 - 2.54 - 1.27 - len("HAT_VBUS_DISCH") * 1.16 - 2.54), 96.52, 134.62, 121.92))   # gate label
        g.add(prow(s, 142.24, 104.14, [("R_100_0805", "HAT_5V", "HAT_DISCH_D"), ("R_100k", "HAT_VBUS_DISCH", "GND")]))
        return g.close()
    grp(f, discharge)
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    f = Flow(s)
    pins = {"1": None, "2": None, "49": None, "50": None}
    for n in range(3, 32, 2):
        pins[str(n)] = "HAT_5V"
    for n in range(4, 33, 2):
        pins[str(n)] = "GND"
    pins.update({"33": "GND", "34": "HAT_CC", "35": "HAT_SSTX_C_P", "36": None, "37": "HAT_SSTX_C_N", "38": None,
                 "39": "GND", "40": None, "41": "HAT_USB3_SSRX_P", "42": "GND", "43": "HAT_USB3_SSRX_N",
                 "44": "HAT_DP_C", "45": "GND", "46": "HAT_DM_C", "47": None, "48": "GND"})
    def receptacle():
        # the 15 VBUS contacts (odd, left) and the ground contacts on the right share one vertical
        # collector each, clear of the signal labels, with one symbol at its end (CRAFT-171)
        g = Group(s, "Flat-cable receptacle: DF40C-50DS (BOM v1 line 66; interface v2 §9.2)")
        hand = {k: "" for k, v in pins.items() if v == "HAT_5V" or (v == "GND" and int(k) % 2 == 0)}
        u = ic(s, "hirose", "DF40C-50DS-0.4V(51)", 101.6, 101.6, {**pins, **hand}, prefix="J",
               extra={"Constraints": "PCB-P-20"})
        side_collector(s, u, [k for k in hand if pins[k] == "HAT_5V"], "HAT_5V", 7.62)
        side_collector(s, u, [k for k in hand if pins[k] == "GND"], "GND", 17.78)
        g.add(u.bbox)
        g.add((u.bbox[0] - 10.16, u.bbox[1] - 5.08, u.bbox[2] + 20.32, u.bbox[3] + 7.62))
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
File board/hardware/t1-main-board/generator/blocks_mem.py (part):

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    xr, _ = put_unit(s, sym, ref, 3, xr + 10.16, 27.94, nets, f)
    xc, yc = put_unit(s, sym, ref, 1, xr + 10.16, 27.94, nets, f)
    s.group_box("ZQ calibration (ADR 0022)", xr + 7.62, yc + 7.62, 48.26, 27.94)   # title clear of the unit
    two_pin_v(s, "R_240", xr + 25.4, yc + 20.32, "vcc0v6_ddr", "DDR_ZQ0", blk)
    put_unit(s, sym, ref, 6, xc + 25.4, 27.94, nets, f)
    # middle band: supplies and ground
    xp, yp = put_unit(s, sym, ref, 4, 25.4, 132.08, nets, f)
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    s.emmc_variants = vv
    # bus unit with the SoC-side parts in front of it; each group box sized from what it holds
    x1, y1 = 25.4, 33.02
    two_pin_h(s, "R_22", x1 + 20.32, y1 + 7.62, "EMMC_CLK", "EMMC_CLK_DEV", blk)
    two_pin_v(s, "R_10k", x1 + 45.72, y1 + 22.86, "vcc_1v8", "EMMC_CMD", blk)
    two_pin_v(s, "R_10k", x1 + 58.42, y1 + 22.86, "vcc_1v8", "EMMC_D0", blk)
    two_pin_v(s, "R_10k", x1 + 71.12, y1 + 22.86, "EMMC_DS", "GND", blk)
    xb, yb = put_unit_variant(s, sym, ref, 1, x1 + 88.9, y1 + 2.54, nets, f, vv)
    xc, yc = put_unit_variant(s, sym, ref, 2, x1 + 88.9, yb + 5.08, nets, f, vv)
    w = snap_up(max(165.1, max(xb, xc) + 2.54 - (x1 - 2.54)))
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    # supplies, below the bus
    x2, y2 = 25.4, snap(y1 - 5.08 + hb + 12.7)   # its title clear of the bus box
    lv = link_variants("LINK_M", variants)
    link(s, "LINK_M", x2 + 25.4, y2 + 10.16, "vcc3v3_sys", "EMMC_VCC", lv)     # source labels inside the box
    link(s, "LINK_M", x2 + 25.4, y2 + 35.56, "vcc_1v8", "EMMC_VCCQ", lv)
    two_pin_v(s, "C_2u2_0402", x2 + 55.88, y2 + 58.42, "EMMC_VDDI", "GND", blk)
    xd, yd = put_unit_variant(s, sym, ref, 3, x2 + 76.2, y2 + 2.54, nets, f, vv)
    xe, ye = put_unit_variant(s, sym, ref, 4, x2 + 76.2, max(y2 + 50.8, snap_up(yd + 5.08)), nets, f, vv)
    s.group_box("Supplies (power tree §4.12 #14, #15)", x2 - 2.54, y2 - 5.08,
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        ["EMMC_CLK", "Input", "Not applicable: blk.emmc is never omitted for boot (BRD-043)"],
        ["EMMC_CMD, EMMC_D0-D7", "Bidirectional", "Pull-ups on CMD and D0 here (HDG p. 26)"],
        ["EMMC_DS", "Output", "Pull-down here (HDG p. 26)"],
        ["EMMC_RST_N", "Input", "SoC ball pull-down at reset (pinout v1)"],
    ]
    corner_notes(s, [
        "1. Function: internal storage, Samsung KLMBG2JETD-B041 eMMC 5.1, 32 GB, 8-bit HS200 (BOM v1",
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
